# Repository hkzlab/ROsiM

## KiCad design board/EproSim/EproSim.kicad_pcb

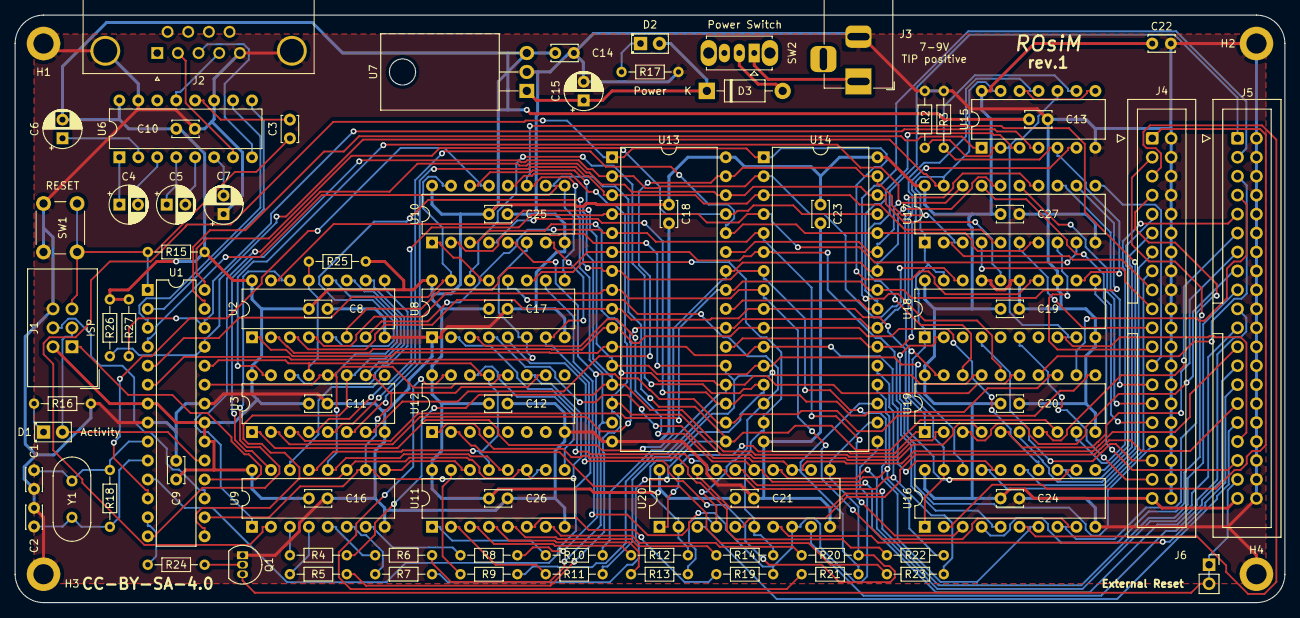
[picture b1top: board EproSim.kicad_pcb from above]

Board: 2 copper layers, 170.2 x 78.7 mm, 88 parts (0 on the bottom side), 141 nets.

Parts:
C1, C2: 22pF; C_Disc_D3.0mm_W2.0mm_P2.50mm
C3, C8, C9, C10, C11, C12, C13, C14, C16, C17, C18, C19, C20, C21, C22, C23, C24, C25, C26, C27: 100nF; C_Disc_D3.4mm_W2.1mm_P2.50mm
C4, C5, C6, C7: 1.0uF; CP_Radial_D5.0mm_P2.50mm
C15: 0.22uF; CP_Radial_D5.0mm_P2.50mm
D1: DATA_LED; LED_D2.0mm_W4.8mm_H2.5mm_FlatTop
D2: POWER_LED; LED_D2.0mm_W4.8mm_H2.5mm_FlatTop
D3: 1N4001; D_DO-41_SOD81_P10.16mm_Horizontal
H1, H2, H3, H4: MountingHole_Pad; MountingHole_2.7mm_M2.5_ISO7380_Pad
J1: AVR-ISP-6; IDC-Header_2x03_P2.54mm_Vertical
J2: RS232; DSUB-9_Female_Horizontal_P2.77x2.84mm_EdgePinOffset4.94mm_H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
J3: Power IN; BarrelJack_Horizontal
J4: EXT_ADDR; IDC-Header_2x20_P2.54mm_Vertical
J5: EXT_D; IDC-Header_2x20_P2.54mm_Vertical
J6: External Reset; PinSocket_1x02_P2.54mm_Vertical
Q1: 2N3904; TO-92_Inline
R2, R3, R4, R5, R6, R7, R8, R9, R10, R11, R12, R13, R14, R15, R19, R20, R21, R22, R23: 10K; R_Axial_DIN0204_L3.6mm_D1.6mm_P7.62mm_Horizontal
R16: 680; R_Axial_DIN0204_L3.6mm_D1.6mm_P7.62mm_Horizontal
R17: 1.2K; R_Axial_DIN0204_L3.6mm_D1.6mm_P7.62mm_Horizontal
R18: 1M; R_Axial_DIN0204_L3.6mm_D1.6mm_P7.62mm_Horizontal
R24: 1K; R_Axial_DIN0204_L3.6mm_D1.6mm_P7.62mm_Horizontal
R25, R26, R27: 4.7K; R_Axial_DIN0204_L3.6mm_D1.6mm_P7.62mm_Horizontal
SW1: SW_Push; SW_PUSH_6mm
SW2: Power; SW_Slide_1P2T_CK_OS102011MS2Q
U1: ATmega8A-PU; DIP-28_W7.62mm
U2, U3, U9, U11, U12: 74HC595; DIP-16_W7.62mm
U6: MAX232; DIP-16_W7.62mm
U7: L7805; TO-220-3_Horizontal_TabDown
U8, U10: 74HC166; DIP-16_W7.62mm
U13, U14: AS6C4008-55PCN; DIP-32_W15.24mm
U15: 74HC32; DIP-14_W7.62mm
U16, U17, U18: 74HCT244; DIP-20_W7.62mm
U19, U20: 74HC244; DIP-20_W7.62mm
Y1: 8Mhz; Crystal_HC49-U_Vertical

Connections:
+12V: J3.1, SW2.1
/EXT_A0: J4.1, U16.2
/EXT_A1: J4.3, U16.4
/EXT_A2: J4.5, U16.6
/EXT_A3: J4.7, U16.8
/EXT_A4: J4.9, U16.11
/EXT_A5: J4.11, U16.13
/EXT_A6: J4.13, U16.15
/EXT_A7: J4.15, U16.17
/EXT_A8: J4.17, U17.2
/EXT_A9: J4.19, U17.4
/EXT_A10: J4.21, U17.6
/EXT_A11: J4.23, U17.8
/EXT_A12: J4.25, U17.11
/EXT_A13: J4.27, U17.13
/EXT_A14: J4.29, U17.15
/EXT_A15: J4.31, U17.17
/EXT_A16: J4.33, U18.2
/EXT_A17: J4.35, U18.4
/EXT_A18: J4.37, U18.6
/EXT_D0: J5.1, U19.18
/EXT_D1: J5.3, U19.16
/EXT_D2: J5.5, U19.14
/EXT_D3: J5.7, U19.12
/EXT_D4: J5.9, U19.9
/EXT_D5: J5.11, U19.7
/EXT_D6: J5.13, U19.5
/EXT_D7: J5.15, U19.3
/EXT_D8: J5.17, U20.18
/EXT_D9: J5.19, U20.16
/EXT_D10: J5.21, U20.14
/EXT_D11: J5.23, U20.12
/EXT_D12: J5.25, U20.9
/EXT_D13: J5.27, U20.7
/EXT_D14: J5.29, U20.5
/EXT_D15: J5.31, U20.3
/MCU_RESET: R24.1, U1.13
/MISO: J1.1, U1.18
/MOSI: J1.4, U1.17
/PISO_CLK: U1.11, U8.7, U10.7
/PISO_INH: U1.6, U8.6, U10.6
/PISO_SER: U1.12, U10.13
/PISO_SH: U1.5, U8.15, U10.15
/RECT_V12: C15.1, D2.2, D3.1, U7.1
/RS232-DTR: J2.4, U6.13
/RS232-RX: J2.2, U6.7
/RS232-TX: J2.3, U6.8
/SCK: D1.2, J1.3, U1.19
/SIPO_CLK: U1.15, U2.11, U3.11, U9.11, U11.11, U12.11
/SIPO_RCLK: U1.23, U2.12, U3.12, U9.12, U11.12, U12.12
/SIPO_SER: U1.14, U2.14
/SRAM_A0: U2.15, U13.12, U14.12, U16.18
/SRAM_A1: U2.1, U13.11, U14.11, U16.16
/SRAM_A2: U2.2, U13.10, U14.10, U16.14
/SRAM_A3: U2.3, U13.9, U14.9, U16.12
/SRAM_A4: U2.4, U13.8, U14.8, U16.9
/SRAM_A5: U2.5, U13.7, U14.7, U16.7
/SRAM_A6: U2.6, U13.6, U14.6, U16.5
/SRAM_A7: U2.7, U13.5, U14.5, U16.3
/SRAM_A8: U3.15, U13.27, U14.27, U17.18
/SRAM_A9: U3.1, U13.26, U14.26, U17.16
/SRAM_A10: U3.2, U13.23, U14.23, U17.14
/SRAM_A11: U3.3, U13.25, U14.25, U17.12
/SRAM_A12: U3.4, U13.4, U14.4, U17.9
/SRAM_A13: U3.5, U13.28, U14.28, U17.7
/SRAM_A14: U3.6, U13.3, U14.3, U17.5
/SRAM_A15: U3.7, U13.31, U14.31, U17.3
/SRAM_A16: U9.15, U13.2, U14.2, U18.18
/SRAM_A17: U9.1, U13.30, U14.30, U18.16
/SRAM_A18: U9.2, U13.1, U14.1, U18.14
/SRAM_D0: R4.2, U10.14, U13.13, U19.2
/SRAM_D1: R5.2, U10.12, U13.14, U19.4
/SRAM_D2: R6.2, U10.11, U13.15, U19.6
/SRAM_D3: R7.2, U10.10, U13.17, U19.8
/SRAM_D4: R8.2, U10.5, U13.18, U19.11
/SRAM_D5: R9.2, U10.4, U13.19, U19.13
/SRAM_D6: R10.2, U10.3, U13.20, U19.15
/SRAM_D7: R11.2, U10.2, U13.21, U19.17
/SRAM_D8: R12.2, U8.14, U14.13, U20.2
/SRAM_D9: R13.2, U8.12, U14.14, U20.4
/SRAM_D10: R14.2, U8.11, U14.15, U20.6
/SRAM_D11: R19.2, U8.10, U14.17, U20.8
/SRAM_D12: R20.2, U8.5, U14.18, U20.11
/SRAM_D13: R21.2, U8.4, U14.19, U20.13
/SRAM_D14: R22.2, U8.3, U14.20, U20.15
/SRAM_D15: R23.2, U8.2, U14.21, U20.17
/SW_12V: D3.2, SW2.2
/TTL-RX: U1.2, U6.9
/TTL-TX: U1.3, U6.10
/XTAL1: C1.2, R18.2, U1.9, Y1.2
/XTAL2: C2.2, R18.1, U1.10, Y1.1
/~EXT_CE: J5.33, U18.8
/~EXT_D_EN: U15.11, U19.1, U19.19, U20.1, U20.19
/~EXT_EN: R26.1, U1.25, U15.13, U16.1, U16.19, U17.1, U17.19, U18.1, U18.19
/~EXT_OE: J5.35, U18.11
/~EXT_RESET: J5.37, J6.1, J6.2, Q1.3
/~PISO_CLR: U1.4, U8.9, U10.9
/~RESET: C3.1, J1.5, R15.2, SW1.2, U1.1
/~SIPO_CLR: U1.16, U2.10, U3.10, U9.10, U11.10, U12.10
/~SIPO_OE: R25.1, U1.24, U2.13, U3.13, U9.13, U11.13, U12.13
/~SRAM_CE: U13.22, U14.22, U15.6
/~SRAM_CE_EXT: R3.1, U15.5, U15.9, U18.12
/~SRAM_CE_MCU: R27.1, U1.26, U15.4
/~SRAM_OE: U13.24, U14.24, U15.3
/~SRAM_OE_EXT: R2.1, U15.2, U15.10, U18.9
/~SRAM_OE_MCU: U1.27, U15.1
/~SRAM_WE: U1.28, U13.29, U14.29
GND: C1.1, C2.1, C7.1, C8.2, C9.2, C10.2, C11.2, C12.2, C13.2, C14.2, C15.2, C16.2, C17.2, C18.2, C19.2, C20.2, C21.2, C22.2, C23.2, C24.2, C25.2, C26.2, C27.2, H1.1, H2.1, H3.1, H4.1, J1.6, J2.0, J2.5, J3.2, J4.2, J4.4, J4.6, J4.8, J4.10, J4.12, J4.14, J4.16, J4.18, J4.20, J4.22, J4.24, J4.26, J4.28, J4.30, J4.32, J4.34, J4.36, J4.38, J4.40, J5.2, J5.4, J5.6, J5.8, J5.10, J5.12, J5.14, J5.16, J5.18, J5.20, J5.22, J5.24, J5.26, J5.28, J5.30, J5.32, J5.34, J5.36, J5.38, J5.40, Q1.1, R2.2, R3.2, R16.2, R17.2, SW1.1, U1.8, U1.22, U2.8, U3.8, U6.11, U6.15, U7.2, U8.1, U8.8, U9.8, U10.8, U11.8, U12.8, U13.16, U14.16, U15.7, U16.10, U17.10, U18.10, U18.13, U18.15, U18.17, U19.10, U20.10
unnamed: C3.2, U6.12
unnamed: C4.1, U6.1
unnamed: C4.2, U6.3
unnamed: C5.1, U6.4
unnamed: C5.2, U6.5
unnamed: C6.1, U6.2
unnamed: C7.2, U6.6
unnamed: D1.1, R16.1
unnamed: D2.1, R17.1
unnamed: Q1.2, R24.2
unnamed: R4.1, U9.3
unnamed: R5.1, U9.4
unnamed: R6.1, U9.5
unnamed: R7.1, U9.6
unnamed: R8.1, U9.7
unnamed: R9.1, U11.15
unnamed: R10.1, U11.1
unnamed: R11.1, U11.2
unnamed: R12.1, U11.3
unnamed: R13.1, U11.4
unnamed: R14.1, U11.5
unnamed: R19.1, U11.6
unnamed: R20.1, U11.7
unnamed: R21.1, U12.15
unnamed: R22.1, U12.1
unnamed: R23.1, U12.2
unnamed: U2.9, U3.14
unnamed: U3.9, U9.14
unnamed: U8.13, U10.1
unnamed: U11.9, U12.14
unnamed: U9.9, U11.14
unnamed: U15.8, U15.12
VCC: C6.2, C8.1, C9.1, C10.1, C11.1, C12.1, C13.1, C14.1, C16.1, C17.1, C18.1, C19.1, C20.1, C21.1, C22.1, C23.1, C24.1, C25.1, C26.1, C27.1, J1.2, J4.39, J5.39, R15.1, R25.2, R26.2, R27.2, U1.7, U1.20, U1.21, U2.16, U3.16, U6.16, U7.3, U8.16, U9.16, U10.16, U11.16, U12.16, U13.32, U14.32, U15.14, U16.20, U17.20, U18.20, U19.20, U20.20

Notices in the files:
board/EproSim/EproSim.kicad_pcb:
CC-BY-SA-4.0
